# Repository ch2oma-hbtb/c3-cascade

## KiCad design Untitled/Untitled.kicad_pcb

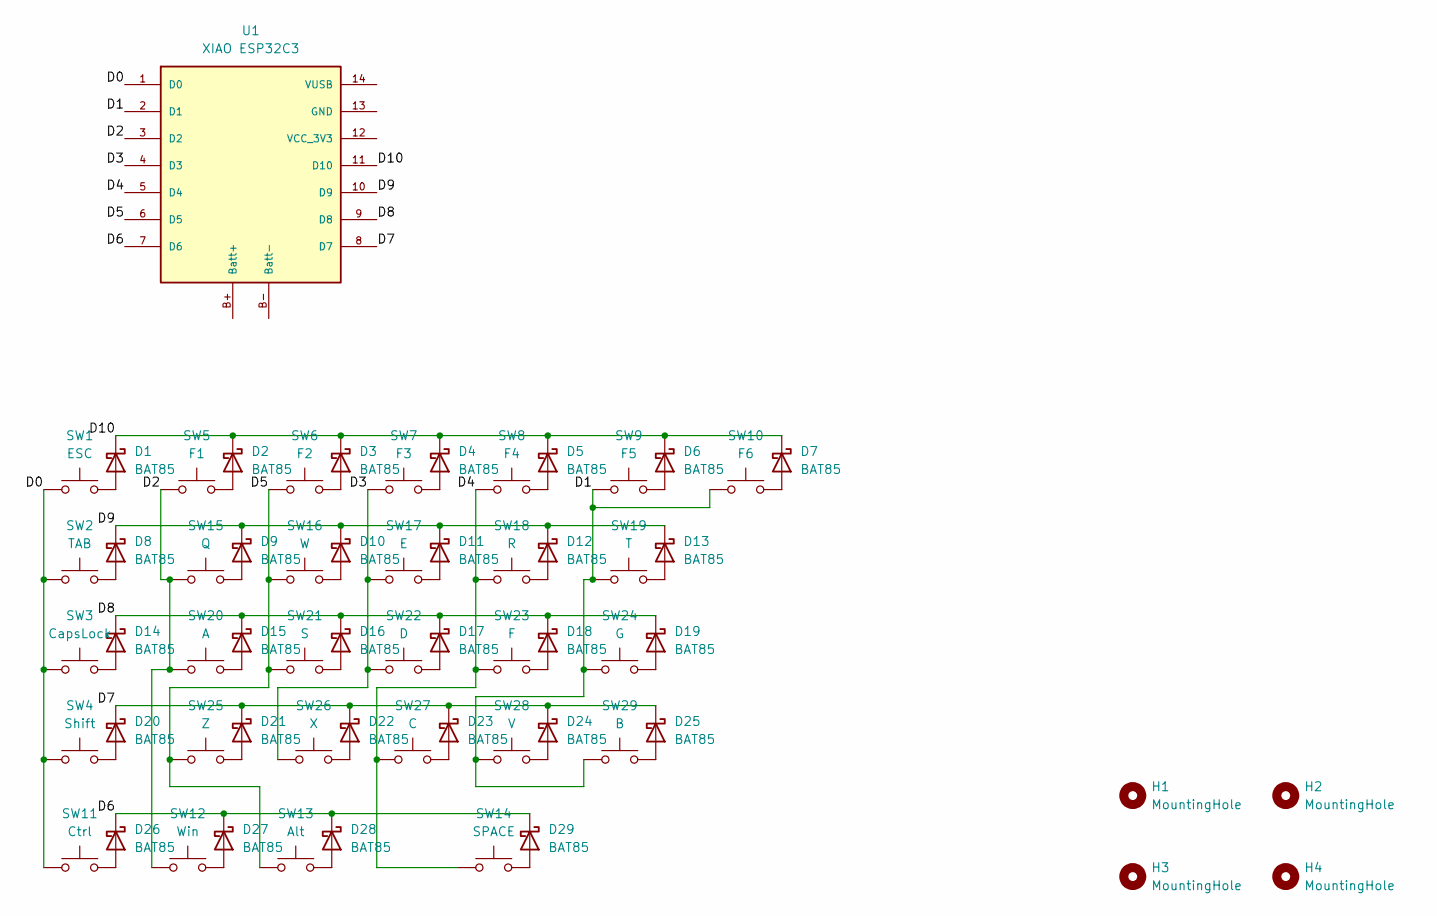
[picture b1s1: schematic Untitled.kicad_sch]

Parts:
D1, D2, D3, D4, D5, D6, D7, D8, D9, D10, D11, D12, D13, D14, D15, D16, D17, D18, D19, D20, D21, D22, D23, D24, D25, D26, D27, D28, D29: BAT85; D_DO-35_SOD27_P7.62mm_Horizontal
H1, H2, H3, H4: MountingHole; MountingHole_3.2mm_M3
SW1: ESC; SW_Cherry_MX_1.00u_Plate
SW2: TAB; SW_Cherry_MX_1.00u_Plate
SW3: CapsLock; SW_Cherry_MX_1.00u_Plate
SW4: Shift; SW_Cherry_MX_1.00u_Plate
SW5: F1; SW_Cherry_MX_1.00u_Plate
SW6: F2; SW_Cherry_MX_1.00u_Plate
SW7: F3; SW_Cherry_MX_1.00u_Plate
SW8: F4; SW_Cherry_MX_1.00u_Plate
SW9: F5; SW_Cherry_MX_1.00u_Plate
SW10: F6; SW_Cherry_MX_1.00u_Plate
SW11: Ctrl; SW_Cherry_MX_1.00u_Plate
SW12: Win; SW_Cherry_MX_1.00u_Plate
SW13: Alt; SW_Cherry_MX_1.00u_Plate
SW14: SPACE; SW_Cherry_MX_1.00u_Plate
SW15: Q; SW_Cherry_MX_1.00u_Plate
SW16: W; SW_Cherry_MX_1.00u_Plate
SW17: E; SW_Cherry_MX_1.00u_Plate
SW18: R; SW_Cherry_MX_1.00u_Plate
SW19: T; SW_Cherry_MX_1.00u_Plate
SW20: A; SW_Cherry_MX_1.00u_Plate
SW21: S; SW_Cherry_MX_1.00u_Plate
SW22: D; SW_Cherry_MX_1.00u_Plate
SW23: F; SW_Cherry_MX_1.00u_Plate
SW24: G; SW_Cherry_MX_1.00u_Plate
SW25: Z; SW_Cherry_MX_1.00u_Plate
SW26: X; SW_Cherry_MX_1.00u_Plate
SW27: C; SW_Cherry_MX_1.00u_Plate
SW28: V; SW_Cherry_MX_1.00u_Plate
SW29: B; SW_Cherry_MX_1.00u_Plate
U1: XIAO ESP32C3; MCU_Seeed_ESP32C3

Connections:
/D0: SW1.1, SW2.1, SW3.1, SW4.1, SW11.1, U1.1 (D0)
/D1: SW9.1, SW10.1, SW19.1, SW24.1, SW28.1, SW29.1, U1.2 (D1)
/D2: SW5.1, SW12.1, SW15.1, SW20.1, U1.3 (D2)
/D3: SW7.1, SW17.1, SW22.1, SW26.1, U1.4 (D3)
/D4: SW8.1, SW14.1, SW18.1, SW23.1, SW27.1, U1.5 (D4)
/D5: SW6.1, SW13.1, SW16.1, SW21.1, SW25.1, U1.6 (D5)
/D6: D26.1 (K), D27.1 (K), D28.1 (K), D29.1 (K), U1.7 (D6)
/D7: D20.1 (K), D21.1 (K), D22.1 (K), D23.1 (K), D24.1 (K), D25.1 (K), U1.8 (D7)
/D8: D14.1 (K), D15.1 (K), D16.1 (K), D17.1 (K), D18.1 (K), D19.1 (K), U1.9 (D8)
/D9: D8.1 (K), D9.1 (K), D10.1 (K), D11.1 (K), D12.1 (K), D13.1 (K), U1.10 (D9)
/D10: D1.1 (K), D2.1 (K), D3.1 (K), D4.1 (K), D5.1 (K), D6.1 (K), D7.1 (K), U1.11 (D10)
unnamed: D1.2 (A), SW1.2
unnamed: D2.2 (A), SW5.2
unnamed: D3.2 (A), SW6.2
unnamed: D4.2 (A), SW7.2
unnamed: D5.2 (A), SW8.2
unnamed: D6.2 (A), SW9.2
unnamed: D7.2 (A), SW10.2
unnamed: D8.2 (A), SW2.2
unnamed: D9.2 (A), SW15.2
unnamed: D10.2 (A), SW16.2
unnamed: D11.2 (A), SW17.2
unnamed: D12.2 (A), SW18.2
unnamed: D13.2 (A), SW19.2
unnamed: D14.2 (A), SW3.2
unnamed: D15.2 (A), SW20.2
unnamed: D16.2 (A), SW21.2
unnamed: D17.2 (A), SW22.2
unnamed: D18.2 (A), SW23.2
unnamed: D19.2 (A), SW24.2
unnamed: D20.2 (A), SW4.2
unnamed: D21.2 (A), SW25.2
unnamed: D22.2 (A), SW26.2
unnamed: D23.2 (A), SW27.2
unnamed: D24.2 (A), SW28.2
unnamed: D25.2 (A), SW29.2
unnamed: D26.2 (A), SW11.2
unnamed: D27.2 (A), SW12.2
unnamed: D28.2 (A), SW13.2
unnamed: D29.2 (A), SW14.2

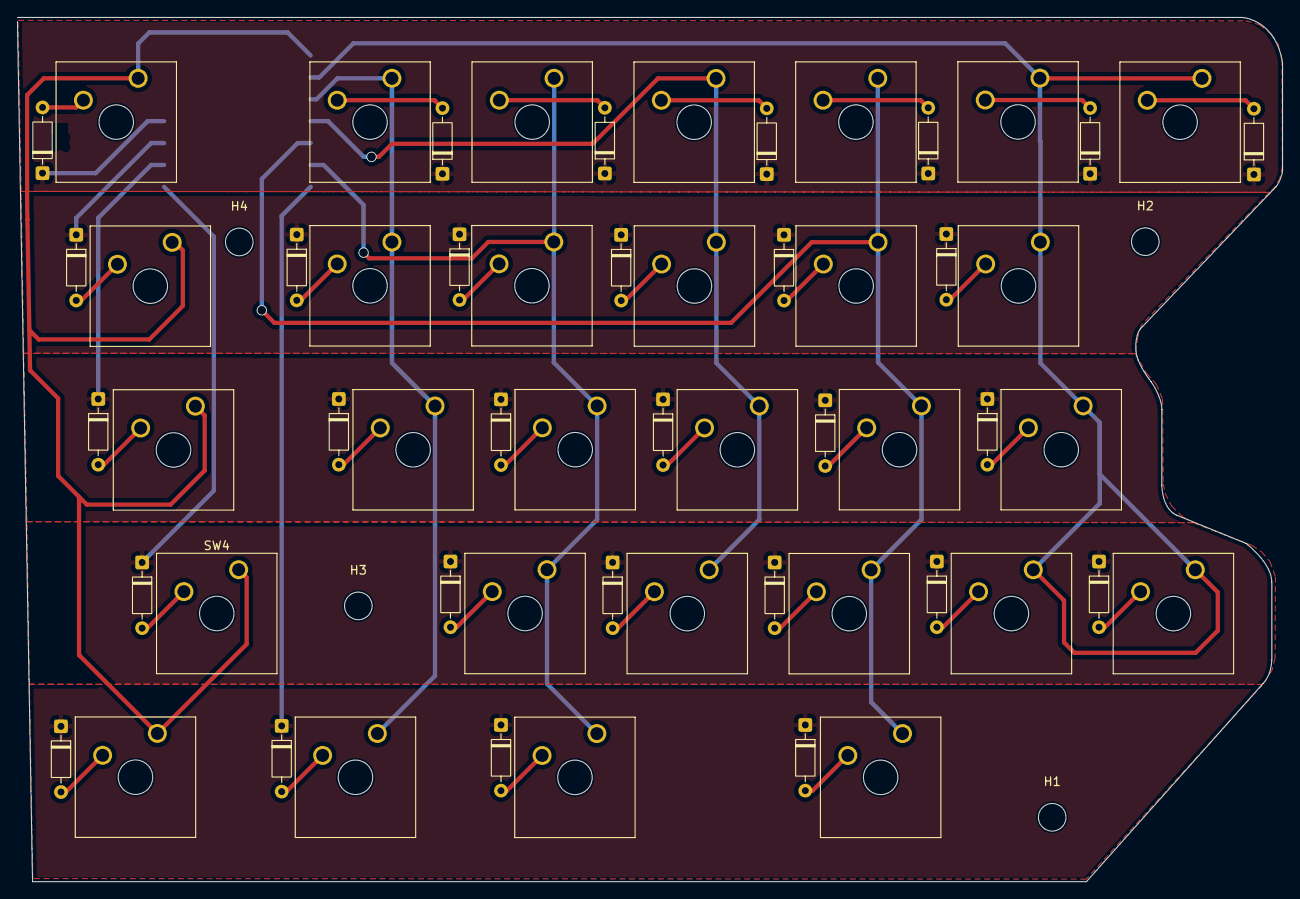
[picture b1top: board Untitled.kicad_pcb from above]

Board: 2 copper layers, 146.8 x 100.2 mm, 63 parts (1 on the bottom side), 40 nets.

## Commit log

2026-04-30 init
2026-05-04 add firmware
2026-05-05 remove unused
2026-05-05 feat: implement WiFi UDP split transport with auto-discovery for non-ESP-NOW platforms
2026-05-06 chore: update cad design file and remove system metadata file
2026-05-07 add layout configuration for RP2040 (RPI PICO W)
2026-05-09 Add support for multiple transport methods and remove WiFi UDP implementation
    - Introduced enum to manage transport types (NONE, ESPNOW, WIFI_UDP).
    - Updated structure to include transport type and IP address for WiFi UDP.
    - Removed the entire file, which handled WiFi UDP communication.
    - Added a new function to reset slave pairing state.
2026-05-09 feat: add FN layer support and adjust deep sleep timeout
